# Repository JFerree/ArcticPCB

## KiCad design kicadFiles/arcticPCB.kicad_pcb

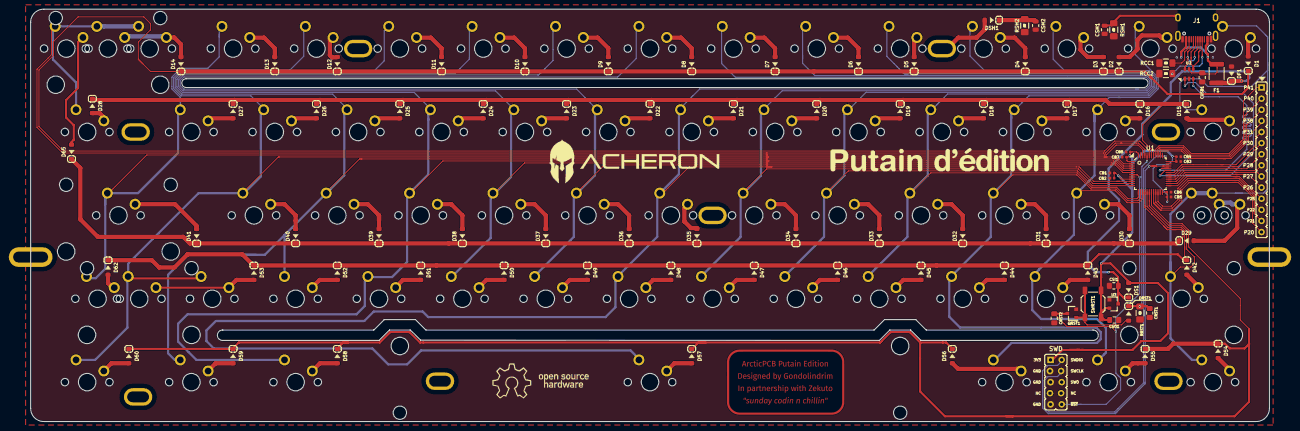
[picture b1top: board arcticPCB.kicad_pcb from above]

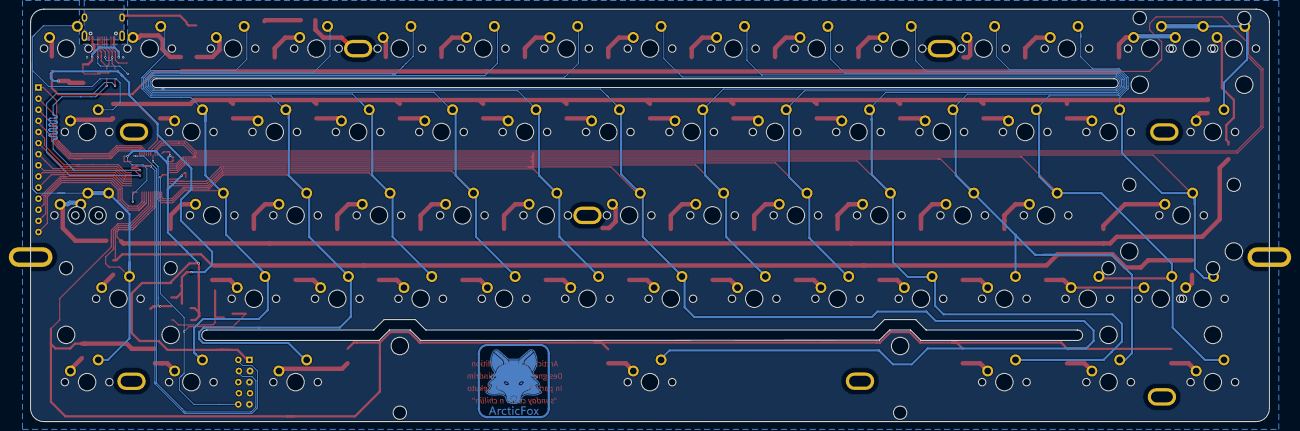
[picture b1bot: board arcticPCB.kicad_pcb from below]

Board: 2 copper layers, 283.0 x 94.2 mm, 176 parts (7 on the bottom side), 113 nets.

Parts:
CB1: 1uF; C_0402_1005Metric
CB2: 10n; C_0402_1005Metric
CB3, CB5, CB8: 100n; C_0402_1005Metric
CB4, CB6: 4.7uF; C_0402_1005Metric
CB7: 100nF; C_0402_1005Metric
CRST1: 10u; C_0805_2012Metric_Pad1.15x1.40mm_HandSolder
CRST2: 4.7n; C_0805_2012Metric_Pad1.15x1.40mm_HandSolder
CSH1, CSH2: 4.7nF; C_0805_2012Metric
CSI1: 100n; C_0805_2012Metric_Pad1.15x1.40mm_HandSolder
CSO1: 100n; C_0805_2012Metric_Pad1.15x1.40mm_HandSolder
CUSB1: 100n; C_0805_2012Metric_Pad1.15x1.40mm_HandSolder
D1, D2, D3, D4, D5, D6, D7, D8, D9, D10, D11, D12, D13, D14, D15, D16, D17, D18, D19, D20, D21, D22, D23, D24, D25, D26, D27, D28, D29, D30, D31, D32, D33, D34, D35, D36, D37, D38, D39, D40, D41, D42, D43, D44, D45, D46, D47, D48, D49, D50, D51, D52, D53, D54, D55, D56, D57, D58, D59, D60, D62, D65: 1N4148; D_SOD-123
DF1: RB060M-60TR; D_SOD-123
DRST1: 1N4148; D_SOD-123
DS1: 1N4148; D_SOD-123
DSH1: 1N4007; D_SOD-123
F1: Polyfuse; Fuse_1812_4532
H1, H6: Half Side Hole; halfSideHole
H2: Mounting Hole; MoutingHole_Oval_7mm_5.0x2.5mm
H3, H4, H5, H7, H8, H9, H10: Oval Mounting Hole; MoutingHole_Oval_7mm_5.0x2.5mm
J1: TYPE-C-31-M12_13; TYPE-C-31-M-12
J2: Conn_01x14; PinHeader_1x14_P2.54mm_Vertical
J3: Conn_ARM_JTAG_SWD_10
L1: ArcticLogo; arcticLogoFilled
L2: OSHLogo; osh-logo
L3: Acheron Logo; acheronLong
L4: ArcticLabel; arcticLabel
L5: Acheron Logo; arcticLabelMask
L6: Putain Logo; putainLogo_50_5
QRST1: DTC123J; SOT-23
RCC1, RCC2: 5.1k; R_SMD_1026
RRST1: 100k; R_SMD_1026
RSH1, RSH2: 1M; R_SMD_1026
SW1: ESC; MX100
SW2: 1; MX100
SW3: 2; MX100
SW4: 3; MX100
SW5: 4; MX100
SW6: 5; MX100
SW7: 6; MX100
SW8: 7; MX100
SW9: 8; MX100
SW10: 9; MX100
SW11: 0; MX100
SW12: -_; MX100
SW13: +=; MX100
SW14: 2U BKSP; MX200
SW15: TAB_150; MX150
SW16: Q; MX100
SW17: W; MX100
SW18: E; MX100
SW19: R; MX100
SW20: T; MX100
SW21: Y; MX100
SW22: U; MX100
SW23: I; MX100
SW24: O; MX100
SW25: P; MX100
SW26: [{; MX100
SW27: ]}; MX100
SW28: \|_150; MX150
SW29: CAPS_175; MX175
SW30: A; MX100
SW31: S; MX100
SW32: D; MX100
SW33: F; MX100
SW34: G; MX100
SW35: H; MX100
SW36: J; MX100
SW37: K; MX100
SW38: L; MX100
SW39: :;; MX100
SW40: "'; MX100
SW41: ENTER_225; MX225
SW42: LSHIFT_225; MX225
SW43: Z; MX100
SW44: X; MX100
SW45: C; MX100
SW46: V; MX100
SW47: B; MX100
SW48: N; MX100
SW49: M; MX100
SW50: <,; MX100
SW51: >.; MX100
SW52: ?/; MX100
SW53: RSHIFT_275; MX275
SW54: LCTRL_150; MX150
SW55: LGUI_100; MX100
SW56: LALT_150; MX150
SW57: SPACE_7U; MX700R
SW58: RALT_150; MX150
SW59: RGUI_100; MX100
SW60: RCTRL_150; MX150
SW61: FN_100; MX100
SW62: RSHIFT_175; MX175
SW63: STEPPED_CAPS_125; MX125
SW64: 1U LBKSP; MX100
SW65: 1U RBKSP; MX100
SWRST1: SW_Push; smdPushBtn
U1: STM32F072-LQFP48; LQFP-48_7x7mm_P0.5mm
U2: USBLC6-2SC6; SOT-23-6
U3: MCP1700-3302E_SOT23; SOT-23

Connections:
3.3V: CB1.2, CB2.2, CB3.2, CB4.2, CB5.2, CB6.2, CB7.1, CB8.2, CSO1.2, DS1.2, J3.1, SWRST1.1, U1.1, U1.9, U1.24, U1.36, U1.48, U3.2
5V: CSI1.2, DF1.1, DS1.1, F1.1, U3.3
/SHIELD: CSH1.2, J1.S, RSH1.1
BOOT0: CRST1.2, DRST1.1, RRST1.1, U1.44
CASE: DSH1.2, H8.1
Col1: SW1.1, SW15.1, SW29.1, SW42.1, SW54.1, SW63.1, U1.18
Col2: SW2.1, SW16.1, SW30.1, SW43.1, SW55.1, U1.15
Col3: SW3.1, SW17.1, SW31.1, SW44.1, SW56.1, U1.14
Col4: SW4.1, SW18.1, SW32.1, SW45.1, U1.13
Col5: SW5.1, SW19.1, SW33.1, SW46.1, U1.12
Col6: SW6.1, SW20.1, SW34.1, SW47.1, U1.11
Col7: SW7.1, SW21.1, SW35.1, SW48.1, SW57.1, U1.10
Col8: SW8.1, SW22.1, SW36.1, SW49.1, U1.6
Col9: SW9.1, SW23.1, SW37.1, SW50.1, U1.5
Col10: SW10.1, SW24.1, SW38.1, SW51.1, SW58.1, U1.4
Col11: SW11.1, SW25.1, SW39.1, SW52.1, SW59.1, U1.3
Col12: SW12.1, SW26.1, SW40.1, SW53.1, SW60.1, SW61.1, U1.2
Col13: SW13.1, SW27.1, SW41.1, SW62.1, U1.46
Col14: SW14.1, SW28.1, SW64.1, SW65.1, U1.45
D+: U1.33, U2.3
D-: U1.32, U2.1
DBus+: J1.A7, J1.B7, U2.4
DBus-: J1.A6, J1.B6, U2.6
Extra1: J2.1, U1.41
Extra2: J2.2, U1.40
Extra3: J2.3, U1.39
Extra4: J2.4, U1.38
Extra5: J2.5, U1.31
Extra6: J2.6, U1.30
Extra7: J2.7, U1.29
Extra8: J2.8, U1.28
Extra9: J2.9, U1.27
Extra10: J2.10, U1.26
Extra11: J2.11, U1.25
Extra12: J2.12, U1.22
Extra13: J2.13, U1.21
Extra14: J2.14, U1.20
GND: CB1.1, CB2.1, CB3.1, CB4.1, CB5.1, CB6.1, CB7.2, CB8.1, CRST1.1, CRST2.2, CSH1.1, CSH2.1, CSI1.1, CSO1.1, CUSB1.1, DF1.2, J1.A1, J1.B1, J3.3, J3.5, J3.9, QRST1.2, RCC1.1, RCC2.1, RRST1.2, RSH1.2, RSH2.2, U1.8, U1.23, U1.35, U1.47, U2.2, U3.1
NRST: CRST2.1, J3.10, QRST1.3, U1.7
unnamed: CSH2.2, DSH1.1, RSH2.1
unnamed: D1.2, SW1.2
unnamed: D2.2, SW2.2
unnamed: D3.2, SW3.2
unnamed: D4.2, SW4.2
unnamed: D5.2, SW5.2
unnamed: D6.2, SW6.2
unnamed: D7.2, SW7.2
unnamed: D8.2, SW8.2
unnamed: D9.2, SW9.2
unnamed: D10.2, SW10.2
unnamed: D11.2, SW11.2
unnamed: D12.2, SW12.2
unnamed: D13.2, SW13.2
unnamed: D14.2, SW14.2, SW64.2
unnamed: D15.2, SW15.2
unnamed: D16.2, SW16.2
unnamed: D17.2, SW17.2
unnamed: D18.2, SW18.2
unnamed: D19.2, SW19.2
unnamed: D20.2, SW20.2
unnamed: D21.2, SW21.2
unnamed: D22.2, SW22.2
unnamed: D23.2, SW23.2
unnamed: D24.2, SW24.2
unnamed: D25.2, SW25.2
unnamed: D26.2, SW26.2
unnamed: D27.2, SW27.2
unnamed: D28.2, SW28.2
unnamed: D29.2, SW29.2, SW63.2
unnamed: D30.2, SW30.2
unnamed: D31.2, SW31.2
unnamed: D32.2, SW32.2
unnamed: D33.2, SW33.2
unnamed: D34.2, SW34.2
unnamed: D35.2, SW35.2
unnamed: D36.2, SW36.2
unnamed: D37.2, SW37.2
unnamed: D38.2, SW38.2
unnamed: D39.2, SW39.2
unnamed: D40.2, SW40.2
unnamed: D41.2, SW41.2
unnamed: D42.2, SW42.2
unnamed: D43.2, SW43.2
unnamed: D44.2, SW44.2
unnamed: D45.2, SW45.2
unnamed: D46.2, SW46.2
unnamed: D47.2, SW47.2
unnamed: D48.2, SW48.2
unnamed: D49.2, SW49.2
unnamed: D50.2, SW50.2
unnamed: D51.2, SW51.2
unnamed: D52.2, SW52.2
unnamed: D53.2, SW53.2, SW61.2
unnamed: D54.2, SW54.2
unnamed: D55.2, SW55.2
unnamed: D56.2, SW56.2
unnamed: D57.2, SW57.2
unnamed: D58.2, SW58.2
unnamed: D59.2, SW59.2
unnamed: D60.2, SW60.2
unnamed: D62.2, SW62.2
unnamed: D65.2, SW65.2
unnamed: DRST1.2, QRST1.1, SWRST1.2
unnamed: J1.A5, RCC2.2
unnamed: J1.B5, RCC1.2
Row1: D1.1, D2.1, D3.1, D4.1, D5.1, D6.1, D7.1, D8.1, D9.1, D10.1, D11.1, D12.1, D13.1, D14.1, U1.43
Row2: D15.1, D16.1, D17.1, D18.1, D19.1, D20.1, D21.1, D22.1, D23.1, D24.1, D25.1, D26.1, D27.1, D28.1, U1.42
Row3: D29.1, D30.1, D31.1, D32.1, D33.1, D34.1, D35.1, D36.1, D37.1, D38.1, D39.1, D40.1, D41.1, D65.1, U1.16
Row4: D42.1, D43.1, D44.1, D45.1, D46.1, D47.1, D48.1, D49.1, D50.1, D51.1, D52.1, D53.1, D62.1, U1.17
Row5: D54.1, D55.1, D56.1, D57.1, D58.1, D59.1, D60.1, U1.19
SWCLK: J3.4, U1.37
SWDIO: J3.2, U1.34
VBUS: CUSB1.2, F1.2, J1.A4, J1.B4, U2.5

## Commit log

2019-12-10 Initial Putain Edition support
